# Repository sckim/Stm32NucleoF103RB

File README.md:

# Stm32NucleoF103RB

**임베디드시스템** 교과목의 실습 자료 저장소이다. STM32 Nucleo-F103RB(ARM Cortex-M3) 보드를 기준으로 GPIO부터 인터럽트, 타이머, ADC, UART, I2C까지 단계별 예제 프로젝트와 참고 문서, 회로 시뮬레이션 파일을 정리한다.

## 개발 환경

* IDE: [VS Code](https://code.visualstudio.com/) + [PlatformIO](https://platformio.org/) (예제 대부분), 일부는 STM32CubeIDE 프로젝트 파일(`.project`, `.cproject`, `.ioc`)을 함께 포함함
* 보드 설정: [STM32CubeMX](https://www.st.com/en/development-tools/stm32cubemx.html)로 생성한 `.ioc` 파일 기준
* 드라이버: STM32 HAL 및 LL(Low-Layer) 라이브러리, 일부 예제는 레지스터 직접 제어 방식
* 회로 시뮬레이션: [Proteus](https://www.labcenter.com/) (프로젝트 파일 `STM32F103R_ArduinoPinmap.pdsprj`는 각 예제 폴더에 있다). 파일이름은 같지만 내부 회로도가 조금씩 다를 수 있다.

## 폴더 구조

| 폴더/파일 | 내용 |
|---|---|
| `Docs/` | 데이터시트, 레퍼런스 매뉴얼 등 STM32F103 관련 공식 문서(PDF) |
| `Examples/` | 실습 예제 프로젝트 모음 |
| `Schematics/AD2_extension/` | AD2 확장 키트 KiCad 회로도/PCB ([README](Schematics/AD2_extension/README.md)) — 2026-10 `01_Lectures` 저장소의 `Schematics/AD2_extension`에서 이동 |

## 문서 활용법

이 저장소는 예제 코드와 함께 여러 층의 문서를 제공한다. 어디에 무엇이 있는지, 무엇을 먼저 여는지를 이 장에서 정리한다. 교안 전체를 어떤 순서로 보면 좋은지는 [교안의_활용법.html](교안의_활용법.html)에 더 자세히 있다.

### 1. 실습을 시작하기 전: 저장소 받기와 최신화

| 문서 | 내용 | 언제 보나 |
|---|---|---|
| [Examples/실습자료_최신화.pdf](Examples/실습자료_최신화.pdf) | VS Code에서 저장소를 클론하고, 수업 전에 Pull로 최신 자료를 받는 절차. 자주 만나는 상황표와 수업 전 체크리스트 | 처음 한 번, 그리고 매 수업 시작 전 |
| [Git_개념과_기본사용법.pdf](Git_개념과_기본사용법.pdf) | Git과 GitHub를 쓰는 이유, Git의 세 작업 공간, 커밋과 GitHub에 올리기, Clone·Pull·Fetch의 차이, 브랜치, 자주 쓰는 명령어, 수업에서 지킬 기본 습관 | 위 절차의 용어가 낯설 때, 내 변경을 기록하고 싶을 때 |

학생은 자료를 내려받기만 한다. 수업에서 지시하지 않았다면 Push나 Sync Changes는 누르지 않는다. 오류나 충돌이 나오면 파일을 지우지 말고 담당자에게 문의한다(자세한 상황표는 `실습자료_최신화.pdf` 4절).

### 2. 문서의 층: 어디에 무엇이 있는가

| 위치 | 문서 | 용도 |
|---|---|---|
| 저장소 루트 | 이 README | 저장소 전체 안내, 예제 목록, 참고 문서, 시뮬레이션 안내 |
| `Examples/` | [Examples/README.md](Examples/README.md) | 예제 전체 지도, 학습 순서, 명명 규칙 |
| 그룹 폴더 (예: `Examples/03_ADC/`) | **`<그룹명> 개념설명.html` (개념설명)** | 그 주변장치가 칩 안에서 어떻게 동작하는지를 원본 블록도와 신호 경로로 이해한다. 그룹별 링크는 아래 [그룹별 개념설명](#그룹별-개념설명)에 있다 |
| 그룹 폴더 | `README.md` | 그룹의 예제 목록, 공통 배선·핀, 배우는 것 |
| 예제 폴더 | `<예제명> 예제설명.html` (예제설명) | 그 예제의 코드를 레지스터·비트 단위로 해석하고, 시뮬레이터·실험·확인 문제로 확인한다. 아직 없는 예제도 있다 |
| 예제 폴더 | `README.md`, `main.c` 상단 주석 | 요약, 사용 레지스터·비트, ISR과 HAL 콜백의 역할 구분 |
| 예제 폴더 | `*.pdsprj`, (`Examples/01_GPIO/02_BlinkHAL`) `wokwi.toml`·`diagram.json` | 보드 없이 시뮬레이션한다. 설정과 제약은 아래 [회로 시뮬레이션](#회로-시뮬레이션) 참고 |
| `Docs/` | RM0008, 데이터시트 등 원본 PDF | 교안이 인용한 쪽을 직접 확인한다. [Docs/README.md](Docs/README.md)에 읽는 순서가 있다 |

### 3. 그룹 하나를 공부하는 순서 (권장)

1. **그룹 `README.md`**: 예제 목록과 필요한 배선을 확인한다.
2. **개념설명 1~3장**: 문제 정의, 일반 개념, 내부 구현 블록도를 먼저 읽는다. 개념과 신호의 흐름을 먼저 잡는다.
3. **예제설명과 코드**: 예제를 번호 순서대로 빌드하고 실행한다. 예제설명이 없는 예제는 예제 README와 `main.c` 주석을 본다.
4. **개념설명 4~7장**: 클럭·시간 계산, 제어 요소, 이벤트, 동작 시나리오를 실습한 예제와 연결해 다시 읽는다.
5. **개념설명 9장 확인 문제**로 점검한다. 답은 접혀 있으므로 먼저 풀어 본 뒤 연다.
6. **막히면** 개념설명 8장(설계상 한계와 정오표)을 보고, 그래도 모르면 `Docs/`의 원본 PDF로 간다.

개념설명 10장의 표는 "각 예제가 개념설명의 어느 장을 쓰는지"를 보여 준다. 예제를 하다가 개념이 막히면 이 표에서 해당 장으로 돌아간다.

### 4. 개념설명은 이렇게 읽는다

개념설명은 모든 그룹이 같은 10장 틀이다. 근거 문서, 인용·표기 약속, 그림 출처처럼 모든 교안에 공통인 내용은 [교안의_활용법.html](교안의_활용법.html)에 한 번만 적었고, 각 교안에는 그 교안만의 내용을 쓴다.

| 장 | 내용 | 이럴 때 본다 |
|---|---|---|
| 1 | 문제 정의 | 이 주변장치가 없으면 CPU가 무엇을 직접 해야 하는지 |
| 2 | 일반 개념 | 칩과 무관한, 디지털논리와 연결되는 기본 원리 |
| 3 | 내부 구현 블록도 | 신호가 핀에서 CPU까지 어떤 경로로 흐르는지 |
| 4 | 클럭 경로와 시간 계산 | 주파수·시간을 계산할 때(계산기 포함) |
| 5 | 제어 요소의 역할 | 레지스터 비트가 블록도의 어느 스위치인지 |
| 6 | 이벤트 생성 기전 | 플래그, 인터럽트, DMA 요청, 다른 주변장치 연결 |
| 7 | 동작 시나리오 | 한 번의 동작을 시간 순서의 타이밍도로 따라갈 때 |
| 8 | 설계상 한계와 이유 | 왜 이렇게 만들었는지, 정오표의 알려진 결함 |
| 9 | 이해 확인 문제 | 계산형·추론형 문제로 점검할 때 |
| 10 | 하부 예제 연결 | 어떤 예제가 이 경로를 쓰는지, 마지막 "정리" 상자 |

읽을 때 알아 둘 점은 다음과 같다.

- **브라우저로 연다.** `.html` 파일을 더블클릭하면 된다. 그림은 같은 그룹 폴더의 `img/`에, PDF 링크는 `Docs/`를 가리키므로 저장소 폴더 구조를 그대로 둔다.
- **그림 캡션의 "출처" 링크**를 누르면 원본 PDF의 그 쪽이 열린다. 교안의 모든 사실은 이렇게 문서의 쪽과 Figure·Table 번호로 확인할 수 있다.
- **"등가 모델" 표시**는 문서에 내부 구현이 없어 디지털논리 소자(카운터, 비교기, 시프트 레지스터 등)로 바꿔 그린 설명이라는 뜻이다. 실제 회로도가 아니다.
- **약어**는 처음 나올 때 풀어 쓰고, 앞쪽의 접힌 "약어 모음"에도 모아 두었다.
- **코드와 라이브러리 함수는 개념설명에 없다.** 코드는 예제설명과 `main.c`에서 다룬다.
- `Examples/12_Advanced_Topics`에는 개념설명이 없다.

## 실습 예제 (`Examples/`)

### 그룹별 개념설명

각 그룹의 주변장치 하드웨어를 원본 블록도와 디지털논리 관점으로 설명하는 문서이다(같은 10장 틀). 예제별 예제설명은 각 예제 폴더에 있다.

| 개념설명 |
|---|
| [01_GPIO](Examples/01_GPIO/01_GPIO%20개념설명.html) |
| [02_USART](Examples/02_USART/02_USART%20개념설명.html) |
| [03_ADC](Examples/03_ADC/03_ADC%20개념설명.html) |
| [04_I2C_Communication](Examples/04_I2C_Communication/04_I2C_Communication%20개념설명.html) |
| [05_SPI_Communication](Examples/05_SPI_Communication/05_SPI_Communication%20개념설명.html) |
| [06_Timers_RTC](Examples/06_Timers_RTC/06_Timers_RTC%20개념설명.html) |
| [07_DMA](Examples/07_DMA/07_DMA%20개념설명.html) |
| [08_Clock_System](Examples/08_Clock_System/08_Clock_System%20개념설명.html) |
| [09_WatchDog_Sleep](Examples/09_WatchDog_Sleep/09_WatchDog_Sleep%20개념설명.html) |
| [10_Flash_CRC](Examples/10_Flash_CRC/10_Flash_CRC%20개념설명.html) |
| [11_CAN_Communication](Examples/11_CAN_Communication/11_CAN_Communication%20개념설명.html) |

### 예제 목록

| 번호 | 예제 (`그룹/예제`) | 구현 방식 | 내용 |
|---|---|---|---|
| 01 | [`01_GPIO/01_BlinkArduino`](Examples/01_GPIO/01_BlinkArduino) | Arduino 프레임워크(PlatformIO) | `pinMode`/`digitalWrite`로 온보드 LED(PA5) 점멸 |
| 02 | [`01_GPIO/02_BlinkHAL`](Examples/01_GPIO/02_BlinkHAL) | HAL 드라이버 | HAL API 기반 LED 점멸 |
| 03 | [`01_GPIO/03_BlinkLL`](Examples/01_GPIO/03_BlinkLL) | LL 드라이버 | LL API 기반 LED 점멸 |
| 04 | [`01_GPIO/04_BlinkReg`](Examples/01_GPIO/04_BlinkReg) | 레지스터 직접 제어 | `RCC`, `GPIOx->CRL` 레지스터를 직접 조작하여 LED 점멸, SysTick 기반 딜레이 구현 |
| 05 | [`01_GPIO/05_ReadPin`](Examples/01_GPIO/05_ReadPin) | HAL | 사용자 버튼(B1) 폴링 입력으로 LED(LD2) 제어 |
| 06 | [`01_GPIO/06_ExtInt`](Examples/01_GPIO/06_ExtInt) | HAL, EXTI | 버튼 입력을 EXTI 인터럽트로 처리(`HAL_GPIO_EXTI_Callback`) |
| 07 | [`01_GPIO/07_ReadPinReg`](Examples/01_GPIO/07_ReadPinReg) | 레지스터 | `GPIOC->IDR` 직접 읽기로 버튼 폴링 (05_ReadPin의 레지스터 버전) |
| 08 | [`01_GPIO/08_ExternalInt`](Examples/01_GPIO/08_ExternalInt) | HAL, EXTI | 두 개 EXTI 라인(`EXTI9_5`, `EXTI15_10`)의 버튼 B1(PC13)·B2(PA6)를 하나의 `HAL_GPIO_EXTI_Callback`에서 구분 처리 |
| 09 | [`01_GPIO/09_BitBandingReg`](Examples/01_GPIO/09_BitBandingReg) | 레지스터 | Cortex-M3 비트 밴딩 별칭으로 RCC/GPIO/SRAM 비트를 원자적으로 접근 |
| 01 | [`02_USART/01_USART_printf`](Examples/02_USART/01_USART_printf) | HAL, UART | `printf` 출력을 USART로 리다이렉션 |
| 02 | [`02_USART/02_USART_Interrupt`](Examples/02_USART/02_USART_Interrupt) | HAL, UART, NVIC | USART2 수신 인터럽트(`HAL_UART_RxCpltCallback`)로 에코 및 LED 제어 |
| 03 | [`02_USART/03_USART_RingBuffer`](Examples/02_USART/03_USART_RingBuffer) | HAL, UART | ISR->main 링 버퍼(lock-free), 오버플로 시험(B1로 main 정지) |
| 04 | [`02_USART/04_USART_DMA_IdleLine_c`](Examples/02_USART/04_USART_DMA_IdleLine_c) | HAL, UART, DMA | (검토 전) DMA 원형 수신 + IDLE 라인 감지로 가변 길이 패킷 처리 |
| 05 | [`02_USART/05_UART_CLI_c`](Examples/02_USART/05_UART_CLI_c) | HAL, UART | (검토 전) 명령줄 인터페이스: 줄 편집, 명령 테이블(help/led/uptime/echo/peek/reset) |
| 06 | [`02_USART/06_USART_HalfDuplex_c`](Examples/02_USART/06_USART_HalfDuplex_c) | HAL, UART | (검토 전) USART 단선 반이중(PA9 한 선), 방향 전환, 오픈드레인 버스 |
| 07 | [`02_USART/07_USART_Stack`](Examples/02_USART/07_USART_Stack) | HAL, UART, CMSIS | 스택(LIFO) 괄호 검사기, ISR 공유 시 경쟁 상태와 PRIMASK 임계 구역 |
| 08 | [`02_USART/08_USART_printf_Dual`](Examples/02_USART/08_USART_printf_Dual) | HAL, UART | `printf`를 USART2(VCP)와 USART1(PA9=D8)로 동시 출력, AD2로 UART 파형 관찰 |
| 01 | [`03_ADC/01_ADC_Single`](Examples/03_ADC/01_ADC_Single) | HAL, ADC | 외부 핀 PA0(CH0) 한 채널 ADC 값을 UART로 출력 |
| 02 | [`03_ADC/02_ADC_Temperature`](Examples/03_ADC/02_ADC_Temperature) | HAL, ADC | 내부 온도 센서(CH16) 값을 섭씨로 환산해 UART로 출력 |
| 03 | [`03_ADC/03_ADC_Multi`](Examples/03_ADC/03_ADC_Multi) | HAL, ADC | 스캔 + 불연속 모드로 DMA 없이 4채널(A0/A1/A2/Vrefint) 폴링 |
| 04 | [`03_ADC/04_ADC_DMA_TimTrigger`](Examples/03_ADC/04_ADC_DMA_TimTrigger) | HAL, ADC, DMA, TIM | TIM3 TRGO 트리거 1kHz 2채널 스캔, DMA 원형 저장, HT/TC 콜백 |
| 05 | [`03_ADC/05_ADC_AnalogWatchdog_c`](Examples/03_ADC/05_ADC_AnalogWatchdog_c) | HAL, ADC, DMA | (검토 전) ADC 아날로그 워치독으로 전압 창(window) 이탈 감지 인터럽트 |
| 06 | [`03_ADC/06_ADC_Vrefint_VDDA_c`](Examples/03_ADC/06_ADC_Vrefint_VDDA_c) | HAL, ADC | (검토 전) Vrefint 로 실제 VDDA 를 측정해 ADC 값을 보정 |
| 07 | [`03_ADC/07_ADC_Potentiometer_PWM_c`](Examples/03_ADC/07_ADC_Potentiometer_PWM_c) | HAL, ADC, TIM | (검토 전) 가변저항 → 이동평균/히스테리시스/감마 → PWM 밝기 |
| 01 | [`04_I2C_Communication/01_I2C_Scan`](Examples/04_I2C_Communication/01_I2C_Scan) | HAL, I2C | I2C1 버스 스캐너(0x08~0x77), 흔한 장치 이름 표시 |
| 02 | [`04_I2C_Communication/02_PCF8574_Output`](Examples/04_I2C_Communication/02_PCF8574_Output) | HAL, I2C | PCF8574 기본: 1바이트로 핀 8개(P7~P0) 출력, 다시 읽어 비교, 액티브 Low LED |
| 03 | [`04_I2C_Communication/03_PCF8574_LCD`](Examples/04_I2C_Communication/03_PCF8574_LCD) | HAL, I2C | PCF8574 I2C 확장 IC를 통한 문자 LCD 제어, I2C 주소 스캐너 포함 |
| 04 | [`04_I2C_Communication/04_I2C_MPU6050_c`](Examples/04_I2C_Communication/04_I2C_MPU6050_c) | HAL, I2C | (검토 전) MPU6050 WHO_AM_I 확인과 가속도/자이로/온도 14바이트 연속 읽기 |
| 05 | [`04_I2C_Communication/05_I2C_MPU6050_DMA_c`](Examples/04_I2C_Communication/05_I2C_MPU6050_DMA_c) | HAL, I2C, DMA | (검토 전) 논블로킹 I2C(DMA)로 MPU6050 읽기, 오류 복구 |
| 06 | [`04_I2C_Communication/06_I2C_OLED_SSD1306_c`](Examples/04_I2C_Communication/06_I2C_OLED_SSD1306_c) | HAL, I2C | (검토 전) SSD1306 OLED, 프레임버퍼, 선/숫자/애니메이션 |
| 07 | [`04_I2C_Communication/07_I2C_EEPROM_AT24C_c`](Examples/04_I2C_Communication/07_I2C_EEPROM_AT24C_c) | HAL, I2C | (검토 전) AT24Cxx EEPROM: 16비트 주소, 페이지 경계, ACK 폴링 |
| 08 | [`04_I2C_Communication/08_I2C_DS3231_RTC_c`](Examples/04_I2C_Communication/08_I2C_DS3231_RTC_c) | HAL, I2C | (검토 전) 외장 RTC DS3231: BCD 시각, 온도, OSF 플래그 |
| 01 | [`05_SPI_Communication/01_SPI_Loopback_c`](Examples/05_SPI_Communication/01_SPI_Loopback_c) | HAL, SPI | (검토 전) SPI1 마스터 루프백(MOSI-MISO 점퍼), 분주비별 전송 속도 측정 |
| 02 | [`05_SPI_Communication/02_SPI_DMA_Fullduplex_c`](Examples/05_SPI_Communication/02_SPI_DMA_Fullduplex_c) | HAL, SPI, DMA | (검토 전) SPI1 전이중 DMA 전송, 폴링 방식과 시간/CPU 여유 비교 |
| 03 | [`05_SPI_Communication/03_SPI_OLED_SSD1306_c`](Examples/05_SPI_Communication/03_SPI_OLED_SSD1306_c) | HAL, SPI | (검토 전) SPI 로 SSD1306 OLED (D/C 핀, 8MHz) |
| 04 | [`05_SPI_Communication/04_SPI_SDcard_c`](Examples/05_SPI_Communication/04_SPI_SDcard_c) | HAL, SPI | (검토 전) SPI 모드 SD 카드 초기화, 섹터 읽기(MBR), 용량 계산 |
| 05 | [`05_SPI_Communication/05_SPI_Flash_W25Qxx_c`](Examples/05_SPI_Communication/05_SPI_Flash_W25Qxx_c) | HAL, SPI | (검토 전) SPI NOR Flash(W25Qxx): JEDEC ID, 섹터 소거, 페이지 프로그램 |
| 06 | [`05_SPI_Communication/06_SPI_MAX7219_c`](Examples/05_SPI_Communication/06_SPI_MAX7219_c) | HAL, SPI | (검토 전) MAX7219 8x8 LED 매트릭스, 16비트 프레임/LOAD 반영 |
| 01 | [`06_Timers_RTC/01_TIM_TimeBase`](Examples/06_Timers_RTC/01_TIM_TimeBase) | HAL, TIM | 타이머 주기 인터럽트(`HAL_TIM_PeriodElapsedCallback`)로 LED 토글 |
| 02 | [`06_Timers_RTC/02_TIM_TimeBase_Polling`](Examples/06_Timers_RTC/02_TIM_TimeBase_Polling) | HAL, TIM | 01의 폴링 버전: `SR.UIF` 직접 확인·클리어, printf 블로킹으로 인한 틱 누락(lag) 관찰 |
| 03 | [`06_Timers_RTC/03_TIM_Overflow_Counter`](Examples/06_Timers_RTC/03_TIM_Overflow_Counter) | HAL+레지스터, TIM | 오버플로 횟수(`gOvf`)를 상위 16비트로 붙인 32비트 µs 시계, 두 번 읽기 경쟁 조건과 UIF 보정
| 04 | [`06_Timers_RTC/04_TIM_OutputCompare`](Examples/06_Timers_RTC/04_TIM_OutputCompare) | HAL, TIM | 출력 비교 Toggle/Timing 모드, CCR 전진으로 채널별 주파수
| 05 | [`06_Timers_RTC/05_TIM_PWM`](Examples/06_Timers_RTC/05_TIM_PWM) | HAL, TIM | TIM2_CH1(PA0) 1kHz PWM, LED 밝기 왕복 |
| 06 | [`06_Timers_RTC/06_TIM_InputCapture_c`](Examples/06_Timers_RTC/06_TIM_InputCapture_c) | HAL, TIM | (검토 전) 입력 캡처로 주기/주파수 측정 (TIM3 PWM 테스트 신호 포함) |
| 07 | [`06_Timers_RTC/07_TIM_PWMInput_c`](Examples/06_Timers_RTC/07_TIM_PWMInput_c) | HAL, TIM | (검토 전) PWM 입력 모드(슬레이브 리셋)로 주파수/듀티 하드웨어 측정 |
| 08 | [`06_Timers_RTC/08_TIM1_DeadTime_Break_c`](Examples/06_Timers_RTC/08_TIM1_DeadTime_Break_c) | HAL, TIM1 | (검토 전) 상보 PWM + 데드타임(약 1us) + 브레이크 입력/소프트웨어 브레이크 |
| 09 | [`06_Timers_RTC/09_TIM_Encoder_c`](Examples/06_Timers_RTC/09_TIM_Encoder_c) | HAL, TIM | (검토 전) 엔코더 인터페이스 모드(x4), 소프트웨어 직교 신호 시뮬레이션 포함 |
| 10 | [`06_Timers_RTC/10_TIM_OnePulse_HCSR04_c`](Examples/06_Timers_RTC/10_TIM_OnePulse_HCSR04_c) | HAL, TIM | (검토 전) 원 펄스 모드 10us 트리거 + 입력 캡처로 HC-SR04 거리 측정 |
| 11 | [`06_Timers_RTC/11_TIM_Servo_c`](Examples/06_Timers_RTC/11_TIM_Servo_c) | HAL, TIM | (검토 전) RC 서보: 50Hz PWM, 1~2ms = 0~180° |
| 12 | [`06_Timers_RTC/12_TIM_MotorDriver_TB6612_c`](Examples/06_Timers_RTC/12_TIM_MotorDriver_TB6612_c) | HAL, TIM | (검토 전) H-브리지 모터: 20kHz PWM, 쇼트 브레이크/코스트, 비상 정지 |
| 13 | [`06_Timers_RTC/13_RTC_Calendar_c`](Examples/06_Timers_RTC/13_RTC_Calendar_c) | HAL+레지스터, RTC | (검토 전) F1 RTC(32비트 카운터)를 Unix 시간으로 쓰는 달력 시계, 1초 인터럽트 |
| 01 | [`07_DMA/01_DMA_MemToMem`](Examples/07_DMA/01_DMA_MemToMem) | HAL, DMA | 메모리->메모리 DMA 복사, CPU 복사와 DWT 사이클 비교 |
| 02 | [`07_DMA/02_DMA_Circular_GPIO`](Examples/07_DMA/02_DMA_Circular_GPIO) | HAL, DMA, TIM | 원형 DMA + 핑퐁 버퍼로 GPIOC 패턴 자동 출력 |
| 01 | [`08_Clock_System/01_CoreRegisters_Instructions_Reg_c`](Examples/08_Clock_System/01_CoreRegisters_Instructions_Reg_c) | 레지스터+ASM | (검토 전) 레지스터 파일, 조건 플래그, IT 조건부실행, 스택 PUSH/POP, 하드웨어 나눗셈 |
| 02 | [`08_Clock_System/02_MemoryMap_Reg_c`](Examples/08_Clock_System/02_MemoryMap_Reg_c) | 레지스터 | (검토 전) 4GB 주소 공간, 버스 계층, memory-mapped I/O, 리틀 엔디안 |
| 03 | [`08_Clock_System/03_ExceptionModel_VectorTable_Reg_c`](Examples/08_Clock_System/03_ExceptionModel_VectorTable_Reg_c) | 레지스터+ASM | (검토 전) 벡터 테이블, 예외 자동 스택 저장, EXC_RETURN, SVC |
| 04 | [`08_Clock_System/04_Clock_Config_Reg_c`](Examples/08_Clock_System/04_Clock_Config_Reg_c) | 레지스터 | (검토 전) RCC/FLASH 레지스터로 HSI 8MHz <-> PLL 48MHz 전환, MCO 출력 |
| 05 | [`08_Clock_System/05_SysTick_Reg_c`](Examples/08_Clock_System/05_SysTick_Reg_c) | 레지스터 | (검토 전) SysTick 1ms 틱, `millis()`, 논블로킹 LED/버튼 처리 |
| 06 | [`08_Clock_System/06_NVIC_Priority_c`](Examples/08_Clock_System/06_NVIC_Priority_c) | HAL, NVIC | (검토 전) 선점/서브 우선순위와 인터럽트 중첩 실험, B1로 3가지 케이스 전환 |
| 07 | [`08_Clock_System/07_AFIO_Remap_Reg_c`](Examples/08_Clock_System/07_AFIO_Remap_Reg_c) | 레지스터 | (검토 전) AFIO_MAPR로 JTAG 핀(PB3/PB4/PA15) 해방과 TIM2 핀 리맵 |
| 08 | [`08_Clock_System/08_HardFault_Diagnosis_Reg_c`](Examples/08_Clock_System/08_HardFault_Diagnosis_Reg_c) | 레지스터+어셈블리 | (검토 전) 4종 폴트 유발, 스택 프레임/CFSR/BFAR 해석해 UART 출력 |
| 09 | [`08_Clock_System/09_MCO_ClockOut_c`](Examples/08_Clock_System/09_MCO_ClockOut_c) | HAL, RCC | (검토 전) MCO(PA8)로 HSI/PLL/HSE 클럭 출력, B1로 소스 순환 |
| 10 | [`08_Clock_System/10_DWT_Profiling_Reg_c`](Examples/08_Clock_System/10_DWT_Profiling_Reg_c) | 레지스터 | (검토 전) DWT 사이클 카운터로 연산/함수 실행 시간(사이클) 측정 |
| 11 | [`08_Clock_System/11_NonBlocking_StateMachine_c`](Examples/08_Clock_System/11_NonBlocking_StateMachine_c) | HAL | (검토 전) HAL_Delay 없는 상태 머신 신호등, 버튼 디바운스/이벤트 |
| 12 | [`08_Clock_System/12_DeviceInfo_UniqueID_Reg_c`](Examples/08_Clock_System/12_DeviceInfo_UniqueID_Reg_c) | 레지스터 | (검토 전) 96비트 고유 ID, 플래시 크기, DEV_ID, 리셋 원인 출력 |
| 01 | [`09_WatchDog_Sleep/01_WatchdogTimer`](Examples/09_WatchDog_Sleep/01_WatchdogTimer) | HAL, WWDG | 윈도우 워치독(WWDG) 초기화와 주기적 리프레시 기본 사용 |
| 02 | [`09_WatchDog_Sleep/02_WWDG_c`](Examples/09_WatchDog_Sleep/02_WWDG_c) | HAL, WWDG | (검토 전) 윈도우 워치독(너무 이른/늦은 리프레시 리셋), 조기 경고 콜백 |
| 03 | [`09_WatchDog_Sleep/03_Sleep_Mode_c`](Examples/09_WatchDog_Sleep/03_Sleep_Mode_c) | HAL, PWR | (검토 전) WFI Sleep 모드, 바쁜 대기와 main 루프 횟수 비교 |
| 04 | [`09_WatchDog_Sleep/04_Stop_Mode_EXTI_c`](Examples/09_WatchDog_Sleep/04_Stop_Mode_EXTI_c) | HAL, PWR, EXTI | (검토 전) Stop 모드 진입, 버튼(EXTI) 웨이크업 후 클럭 복구 |
| 05 | [`09_WatchDog_Sleep/05_Standby_RTC_Wakeup_c`](Examples/09_WatchDog_Sleep/05_Standby_RTC_Wakeup_c) | HAL, PWR, RTC | (검토 전) Standby 진입, RTC 알람(10초) 웨이크업, BKP 부팅 카운터 유지 |
| 06 | [`09_WatchDog_Sleep/06_BKP_Tamper_c`](Examples/09_WatchDog_Sleep/06_BKP_Tamper_c) | HAL+레지스터, BKP | (검토 전) 백업 레지스터 유지, TAMPER(PC13) 감지 시 삭제 |
| 07 | [`09_WatchDog_Sleep/07_IWDG_c`](Examples/09_WatchDog_Sleep/07_IWDG_c) | HAL, IWDG | (검토 전) 독립 워치독(LSI), 타임아웃 계산, 리셋 원인 |
| 01 | [`10_Flash_CRC/01_Flash_Write_c`](Examples/10_Flash_CRC/01_Flash_Write_c) | HAL, FLASH | (검토 전) 내부 Flash 페이지에 부팅 횟수 덧붙여 저장(웨어 레벨링) |
| 02 | [`10_Flash_CRC/02_CRC_Unit_c`](Examples/10_Flash_CRC/02_CRC_Unit_c) | HAL, CRC | (검토 전) 하드웨어 CRC-32/MPEG-2와 소프트웨어 구현 비교, 1비트 오류 검출 |
| 01 | [`11_CAN_Communication/01_CAN_Loopback_c`](Examples/11_CAN_Communication/01_CAN_Loopback_c) | HAL, CAN | (검토 전) bxCAN 500kbps 루프백 송수신(트랜시버 불필요), FIFO0 수신 콜백 |
| 02 | [`11_CAN_Communication/02_CAN_Filter_c`](Examples/11_CAN_Communication/02_CAN_Filter_c) | HAL, CAN | (검토 전) bxCAN 수신 필터: ID 리스트/마스크, 표준·확장, FIFO0/1 |
| 01 | [`12_Advanced_Topics/01_ADC_Injected_c`](Examples/12_Advanced_Topics/01_ADC_Injected_c) | HAL, ADC, DMA | (검토 전) 주입 채널이 정규 연속 변환에 끼어들어 온도 센서를 읽음 |
| 02 | [`12_Advanced_Topics/02_ADC_DualMode_c`](Examples/12_Advanced_Topics/02_ADC_DualMode_c) | HAL, ADC, DMA | (검토 전) ADC1+ADC2 동시 샘플링(듀얼 모드), 32비트 DMA |
| 03 | [`12_Advanced_Topics/03_I2C_Slave_Loopback_c`](Examples/12_Advanced_Topics/03_I2C_Slave_Loopback_c) | HAL, I2C | (검토 전) I2C 슬레이브 모드(I2C1 마스터 ↔ I2C2 슬레이브), 리슨/주소 콜백 |
| 04 | [`12_Advanced_Topics/04_SPI_Slave_Loopback_c`](Examples/12_Advanced_Topics/04_SPI_Slave_Loopback_c) | HAL, SPI | (검토 전) SPI 슬레이브 모드(SPI1 마스터 ↔ SPI2 슬레이브), 하드웨어 NSS |
| 05 | [`12_Advanced_Topics/05_TIM_Cascade32_c`](Examples/12_Advanced_Topics/05_TIM_Cascade32_c) | HAL, TIM | (검토 전) 마스터/슬레이브로 잇는 32비트 카운터(71분), 스톱워치 |
| 06 | [`12_Advanced_Topics/06_DMA_Priority_c`](Examples/12_Advanced_Topics/06_DMA_Priority_c) | HAL, DMA | (검토 전) DMA 채널 우선순위/중재, 완료 시각 DWT 측정 |
| 07 | [`12_Advanced_Topics/07_PendSV_ContextSwitch_Reg_c`](Examples/12_Advanced_Topics/07_PendSV_ContextSwitch_Reg_c) | 레지스터+어셈블리 | (검토 전) SVC/PendSV/PSP 기반 미니 선점형 RTOS(작업 2개 시분할) |
| 08 | [`12_Advanced_Topics/08_HSE_PLL_72MHz_Reg_c`](Examples/12_Advanced_Topics/08_HSE_PLL_72MHz_Reg_c) | 레지스터 | (검토 전) HSE(바이패스)+PLL x9 = 72MHz, 실패 시 HSI 로 복귀 |
| 09 | [`12_Advanced_Topics/09_ITM_SWO_Printf_Reg_c`](Examples/12_Advanced_Topics/09_ITM_SWO_Printf_Reg_c) | 레지스터 | (검토 전) ITM/SWO 로 printf (UART 핀 불필요) |
| 10 | [`12_Advanced_Topics/10_StackWatermark_Reg_c`](Examples/12_Advanced_Topics/10_StackWatermark_Reg_c) | 레지스터 | (검토 전) 스택 페인팅과 하이 워터마크, 재귀 실험 |
| 11 | [`12_Advanced_Topics/11_IAP_Bootloader_Reg_c`](Examples/12_Advanced_Topics/11_IAP_Bootloader_Reg_c) | 레지스터 | (검토 전) IAP 부트로더: 앱 유효성 검사 후 VTOR 교체·점프 (링커 스크립트 포함) |
| 12 | [`12_Advanced_Topics/12_IAP_App_Reg_c`](Examples/12_Advanced_Topics/12_IAP_App_Reg_c) | 레지스터 | (검토 전) 0x08008000 에서 도는 IAP 응용 프로그램 (부트로더와 짝) |
| 13 | [`12_Advanced_Topics/13_IAP_Xmodem_Bootloader_Reg_c`](Examples/12_Advanced_Topics/13_IAP_Xmodem_Bootloader_Reg_c) | 레지스터 | (검토 전) UART XMODEM-CRC 로 펌웨어 수신·Flash 기록·점프하는 부트로더 |
| 14 | [`12_Advanced_Topics/14_OptionBytes_Read_c`](Examples/12_Advanced_Topics/14_OptionBytes_Read_c) | HAL, FLASH | (검토 전) 옵션 바이트 읽기(RDP/WRP/USER), 읽기 전용 |
| 15 | [`12_Advanced_Topics/15_CAN_Normal_2boards_c`](Examples/12_Advanced_Topics/15_CAN_Normal_2boards_c) | HAL, CAN | (검토 전) 실제 CAN 버스(2보드): 오류 카운터, 버스오프 복구 |

예제는 기능별 그룹 폴더 아래에 있고, **예제 폴더 번호는 그룹 안에서 항상 `01`부터 순서대로** 붙인다. 폴더명 끝의 `_c`는 Claude가 작성한 예제(검토 전)를 뜻한다. `12_Advanced_Topics`는 3학년 2학기 기본 진도를 넘어서는 **심화(선택)** 예제만 모아 둔 그룹이며, 나머지 01~11 그룹이 한 학기 분량이다. 그룹별 안내는 [Examples/README.md](Examples/README.md) 참고.

각 예제 폴더는 PlatformIO 프로젝트(`platformio.ini` 포함) 또는 STM32CubeIDE 프로젝트(`.project`/`.cproject`/`.ioc` 포함) 형태이며, VS Code에서 PlatformIO 확장으로 열어 빌드·업로드하는 것을 기본으로 한다.

## 참고 문서 (`Docs/`)

각 문서의 용도, 처음 읽는 순서, RM0008/PM0056 장 지도, 보드 클럭 구성은 [Docs/README.md](Docs/README.md) 에 정리되어 있다.

| 문서 | 설명 |
|---|---|
| [UM1724](Docs/UM1724_User_Manual_STM32Nucleo64.pdf) | Nucleo-64 보드 사용자 매뉴얼 |
| [DS5319 (데이터시트)](Docs/Datasheet_stm32f103.pdf) | STM32F103x8/xB 데이터시트 |
| [RM0008](Docs/RM0008_Reference_manual.pdf) | STM32F101/102/103/105/107 레지스터 레퍼런스 매뉴얼 |
| [PM0056](Docs/PM0056_CortexM3_Programming_Manual.pdf) | Cortex-M3 프로그래밍 매뉴얼 |
| [UM1850](Docs/HAL_UM1850_hal_and_lowlayer_drivers.pdf) | STM32F1 HAL/LL 드라이버 사용자 매뉴얼 |
| [MB1136 회로도](Docs/Schematic_STM32F103RB.pdf) | Nucleo-F103RB 보드 회로도 |
| [UM1718 (st.com)](https://www.st.com/resource/en/user_manual/um1718-stm32cubemx.pdf) | STM32CubeMX 사용자 매뉴얼 (77MB라 저장소에 넣지 않고 ST 사이트로 연결) |
| [PM0075](Docs/PM0075-stm32f10xxx-flash-memory.pdf) | STM32F10xxx Flash 메모리 프로그래밍 매뉴얼(쓰기·지우기·옵션 바이트) |
| [ES096](Docs/ES096_F103x8xB_Errata.pdf) | STM32F103x8/xB(중밀도, F103RB) 디바이스 errata(오류 정정표) |
| [AN2834](https://github.com/sckim/Stm32NucleoF103RB/blob/main/Docs/AN2834_ADC_Accuracy.pdf) | ADC 정확도 최적화 |
| [AN4013](https://github.com/sckim/Stm32NucleoF103RB/blob/main/Docs/AN4013_Timers_Introduction.pdf) | STM32 타이머 개요 |
| [AN4776](https://github.com/sckim/Stm32NucleoF103RB/blob/main/Docs/AN4776_General_Purpose_Timer.pdf) | 범용 타이머 활용 |
| [AN2548](https://github.com/sckim/Stm32NucleoF103RB/blob/main/Docs/AN2548_DMA_Controller.pdf) | DMA 컨트롤러 사용법 |
| [AN2586](Docs/AN2586_Hardware_Development_Getting_Started.pdf) | STM32F10xxx 하드웨어 개발 시작 가이드 |
| [AN2606](Docs/AN2606_System_Memory_Boot_Mode.pdf) | STM32 시스템 메모리 부트 모드(부트로더) |
| [DB2196](Docs/DB2196_Nucleo_64_boards.pdf) | Nucleo-64 보드 데이터브리프 |
| [UM1727](Docs/UM1727_Getting_started.pdf) | Nucleo 보드 시작하기 가이드(2016, 오래된 도구 기준) |
| [NUCLEO-F103RB 제품 페이지 (st.com)](https://www.st.com/en/evaluation-tools/nucleo-f103rb.html?ecmp=tt9470_gl_link_feb2019&rt=db&id=DB2196) | ST 공식 제품 페이지 (`Docs/NUCLEO-F103RB.url` 바로가기와 같은 주소) |

## 회로 시뮬레이션
Proteus 프로젝트는 각 예제 폴더에 있다. 파일 이름은 `STM32F103R_ArduinoPinmap.pdsprj`이다(`01_GPIO/07_ReadPinReg`만 `STM32F103R.pdsprj`). Proteus에서 열 때 MCU의 펌웨어 경로(`firmware.elf`)를 해당 예제의 빌드 결과로 지정한다.

### Proteus의 MCU 모델: F103RB 대신 F103C8

Proteus(8.17 기준) 라이브러리에는 **STM32F103RB 모델이 없다**. 제공되는 STM32F103 부품은 C4, C6, C8, R4, R6, T4, T6뿐이다. 그래서 프로젝트의 MCU는 그중 F103RB와 같은 medium-density 칩인 **STM32F103C8**(48핀)을 쓴다. 파일 이름에 `R`이 들어 있지만 실제 MCU는 C8이다.

| 항목 | STM32F103C8 (Proteus) | STM32F103RB (Nucleo) |
|---|---|---|
| 계열 | medium-density | medium-density |
| SRAM | 20 KB | 20 KB |
| 주변장치 | TIM1~4, SPI1~2, I2C1~2, USART1~3, USB, CAN | 같음 |
| Flash | **64 KB** | 128 KB |
| 패키지 / GPIO | **48핀 / 37개** | 64핀 / 51개 |

같은 계열이라 레지스터 주소, 주변장치 구성, 인터럽트 벡터, DMA 채널 배정은 같다(DS5319 Table 2). 차이는 Flash 크기와 핀 수이다.

- **포트 C가 거의 없다**: 48핀 패키지에는 **PC0~PC12와 PD2가 없고, 포트 C는 PC13~PC15만 있다**. Nucleo Arduino 헤더 가운데 포트 C에 연결된 핀(D9 = PC7, A4 = PC1, A5 = PC0 등)을 쓰는 예제는 Proteus에서 그 핀을 시뮬레이션할 수 없다(예: `01_GPIO/10_AD2Test`). PA·PB 핀과 PC13(사용자 버튼 B1)만 쓰는 예제는 문제없다.
- **Flash 64 KB**: 펌웨어가 64 KB를 넘으면 C8 모델에 올라가지 않는다. 현재 예제들은 대부분 이보다 훨씬 작다.
- 64핀 R6 모델은 핀은 맞지만 low-density 칩이다. Flash가 작고 TIM4·USART3·I2C2·SPI2 같은 medium-density 주변장치가 없어 RB용 펌웨어와 맞지 않는다.

Proteus의 STM32 모델 파일에는 DMA, RTC, IWDG, WWDG, ADC, USB 등의 모델이 들어 있다. 반면 **저전력 모드(PWR의 Sleep/Stop/Standby), 백업 레지스터·탬퍼(BKP), CAN은 모델링되어 있지 않은 것으로 보인다**. 이 판단은 설치된 모델 파일을 분석한 결과이다(Labcenter의 공식 목록은 없다). `09_WatchDog_Sleep`의 저전력·BKP 예제와 `11_CAN_Communication`은 실제 보드로 확인한다.

### Wokwi

`01_GPIO/02_BlinkHAL`에는 [Wokwi](https://wokwi.com) 시뮬레이터 설정(`wokwi.toml`, `diagram.json`)도 있다. Wokwi 역시 F103RB가 없어 Blue Pill(STM32F103C8)을 쓰며, DMA·RTC·PWR·IWDG는 지원하지 않는다. 사용법은 그 예제의 README를 참고한다.

## 관련 교과목
- 디지털논리회로, 디지털시스템, 마이크로컨트롤러
- 프로그래밍 언어 (C or C++)
- 회로이론, 전자회로

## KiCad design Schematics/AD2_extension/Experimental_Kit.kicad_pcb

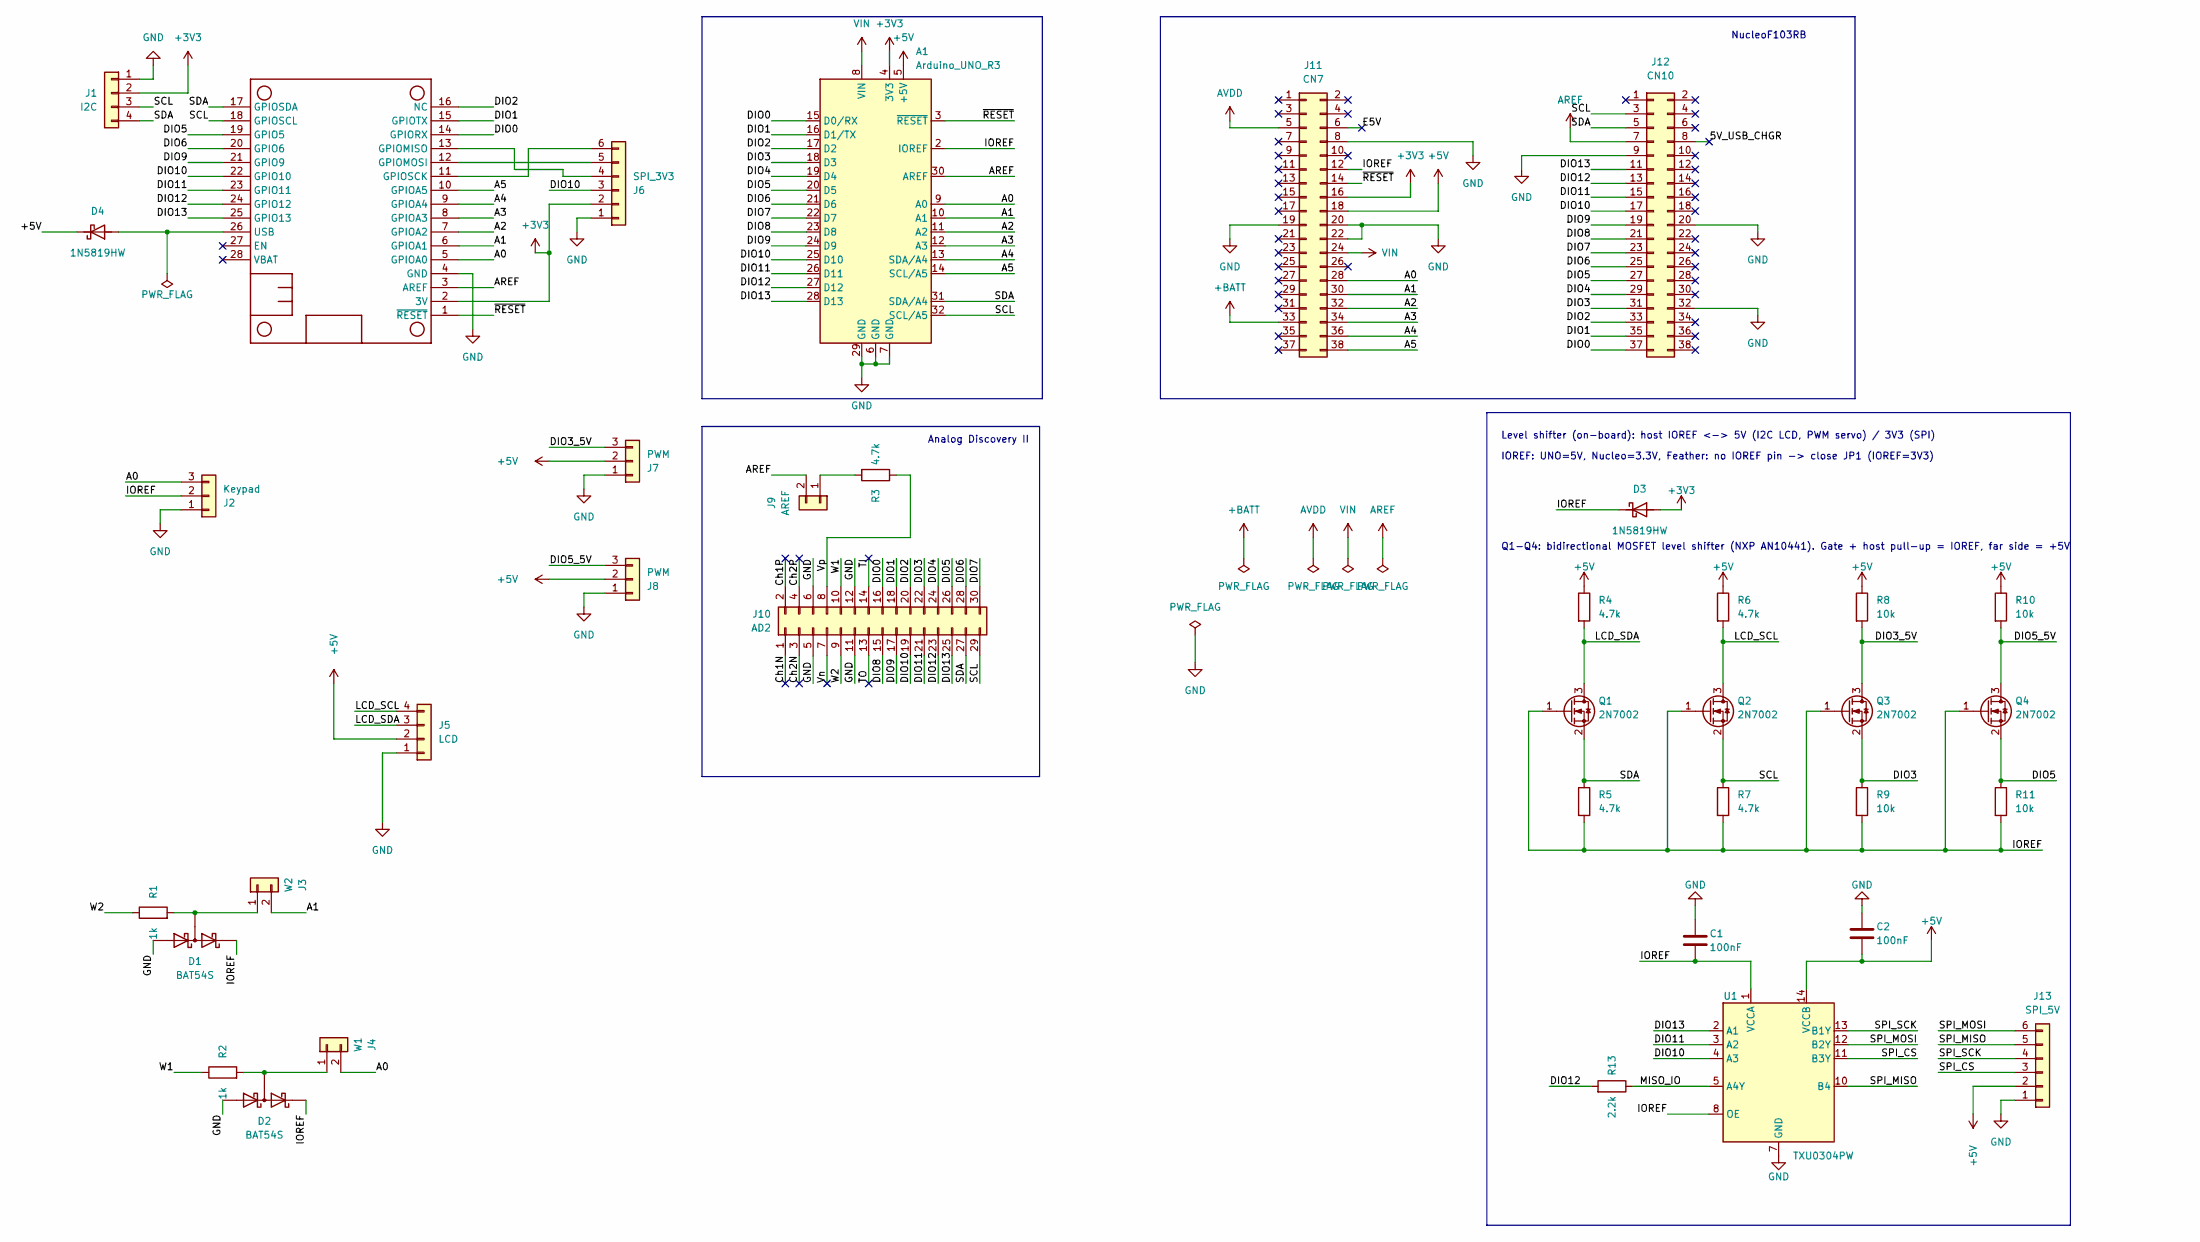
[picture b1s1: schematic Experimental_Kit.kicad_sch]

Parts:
A1: Arduino_UNO_R3; Arduino_UNO_R3_ShieldHeaders
C1, C2: 100nF; C_0805_2012Metric_Pad1.18x1.45mm_HandSolder
D1, D2: BAT54S; SOT-23
D3, D4: 1N5819HW; D_SOD-123
J1: I2C; PinHeader_1x04_P2.54mm_Vertical
J2: Keypad; PinHeader_1x03_P2.54mm_Vertical
J3: W2; PinHeader_1x02_P2.54mm_Vertical
J4: W1; PinHeader_1x02_P2.54mm_Vertical
J5: LCD; PinHeader_1x04_P2.54mm_Vertical
J6: SPI_3V3; PinHeader_1x06_P2.54mm_Vertical
J7, J8: PWM; PinHeader_1x03_P2.54mm_Vertical
J9: AREF; PinHeader_1x02_P2.54mm_Vertical
J10: AD2; PinSocket_2x15_P2.54mm_Horizontal_BoardEdge
J11: CN7; PinSocket_2x19_P2.54mm_Vertical_Mirrored
J12: CN10; PinSocket_2x19_P2.54mm_Vertical_Mirrored
J13: SPI_5V; PinHeader_1x06_P2.54mm_Vertical
MS1: FEATHERWING_NODIM
Q1, Q2, Q3, Q4: 2N7002; SOT-23
R1, R2: 1k; R_0805_2012Metric_Pad1.20x1.40mm_HandSolder
R3, R4, R5, R6, R7: 4.7k; R_0805_2012Metric_Pad1.20x1.40mm_HandSolder
R8, R9, R10, R11: 10k; R_0805_2012Metric_Pad1.20x1.40mm_HandSolder
R13: 2.2k; R_0805_2012Metric_Pad1.20x1.40mm_HandSolder
U1: TXU0304PW; TSSOP-14_4.4x5mm_P0.65mm

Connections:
+3V3: A1.4 (3V3), D3.2 (A), J1.2, J6.2, J11.16, MS1.2 (3V)
+5V: A1.5 (+5V), C2.2, D4.1 (K), J5.2, J7.2, J8.2, J11.18, J13.2, R4.1, R6.1, R8.1, R10.1, U1.14 (VCCB)
+BATT: J11.33
/5V_USB_CHGR: J12.8
/A0: A1.9 (A0), J2.3, J4.2, J11.28, MS1.5 (GPIOA0)
/A1: A1.10 (A1), J3.2, J11.30, MS1.6 (GPIOA1)
/A2: A1.11 (A2), J11.32, MS1.7 (GPIOA2)
/A3: A1.12 (A3), J11.34, MS1.8 (GPIOA3)
/A4: A1.13 (SDA/A4), J11.36, MS1.9 (GPIOA4)
/A5: A1.14 (SCL/A5), J11.38, MS1.10 (GPIOA5)
/Ch1N: J10.1
/Ch1P: J10.2
/Ch2N: J10.3
/Ch2P: J10.4
/DIO0: A1.15 (D0/RX), J10.16, J12.37, MS1.14 (GPIORX)
/DIO1: A1.16 (D1/TX), J10.18, J12.35, MS1.15 (GPIOTX)
/DIO2: A1.17 (D2), J10.20, J12.33, MS1.16 (NC)
/DIO3: A1.18 (D3), J10.22, J12.31, Q3.2 (S), R9.1
/DIO3_5V: J7.3, Q3.3 (D), R8.2
/DIO4: A1.19 (D4), J10.24, J12.29
/DIO5: A1.20 (D5), J10.26, J12.27, MS1.19 (GPIO5), Q4.2 (S), R11.1
/DIO5_5V: J8.3, Q4.3 (D), R10.2
/DIO6: A1.21 (D6), J10.28, J12.25, MS1.20 (GPIO6)
/DIO7: A1.22 (D7), J10.30, J12.23
/DIO8: A1.23 (D8), J10.15, J12.21
/DIO9: A1.24 (D9), J10.17, J12.19, MS1.21 (GPIO9)
/DIO10: A1.25 (D10), J6.3, J10.19, J12.17, MS1.22 (GPIO10), U1.4 (A3)
/DIO11: A1.26 (D11), J10.21, J12.15, MS1.23 (GPIO11), U1.3 (A2)
/DIO12: A1.27 (D12), J10.23, J12.13, MS1.24 (GPIO12), R13.2
/DIO13: A1.28 (D13), J10.25, J12.11, MS1.25 (GPIO13), U1.2 (A1)
/E5V: J11.6
/IOREF: A1.2 (IOREF), C1.2, D1.2 (K2), D2.2 (K2), D3.1 (K), J2.2, J11.12, Q1.1 (G), Q2.1 (G), Q3.1 (G), Q4.1 (G), R5.2, R7.2, R9.2, R11.2, U1.1 (VCCA), U1.8 (OE)
/LCD_SCL: J5.4, Q2.3 (D), R6.2
/LCD_SDA: J5.3, Q1.3 (D), R4.2
/MISO_IO: R13.1, U1.5 (A4Y)
/SCL: A1.32 (SCL/A5), J1.3, J10.29, J12.3, MS1.18 (GPIOSCL), Q2.2 (S), R7.1
/SDA: A1.31 (SDA/A4), J1.4, J10.27, J12.5, MS1.17 (GPIOSDA), Q1.2 (S), R5.1
/SPI_CS: J13.3, U1.11 (B3Y)
/SPI_MISO: J13.5, U1.10 (B4)
/SPI_MOSI: J13.6, U1.12 (B2Y)
/SPI_SCK: J13.4, U1.13 (B1Y)
/TI: J10.14
/TO: J10.13
/Vn: J10.7
/Vp: J10.8, R3.1
/W1: J10.10, R2.1
/W2: J10.9, R1.1
/~RESET: A1.3 (~RESET), J11.14, MS1.1 (~RESET)
AREF: A1.30 (AREF), J9.2, J12.7, MS1.3 (AREF)
AVDD: J11.5
GND: A1.6 (GND), A1.7 (GND), A1.29 (GND), C1.1, C2.1, D1.1 (A1), D2.1 (A1), J1.1, J2.1, J5.1, J6.1, J7.1, J8.1, J10.5, J10.6, J10.11, J10.12, J11.8, J11.19, J11.20, J11.22, J12.9, J12.20, J12.32, J13.1, MS1.4 (GND), U1.7 (GND)
unnamed: D1.3 (K1A2), J3.1, R1.2
unnamed: D2.3 (K1A2), J4.1, R2.2
unnamed: D4.2 (A), MS1.26 (USB)
unnamed: J6.4, MS1.13 (GPIOMISO)
unnamed: J6.5, MS1.12 (GPIOMOSI)
unnamed: J6.6, MS1.11 (GPIOSCK)
unnamed: J9.1, R3.2
VIN: A1.8 (VIN), J11.24

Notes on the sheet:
Level shifter (on-board): host IOREF <-> 5V (I2C LCD, PWM servo) / 3V3 (SPI)
IOREF: UNO=5V, Nucleo=3.3V, Feather: no IOREF pin -> close JP1 (IOREF=3V3)
Q1-Q4: bidirectional MOSFET level shifter (NXP AN10441). Gate + host pull-up = IOREF, far side = +5V
NucleoF103RB
Analog Discovery II

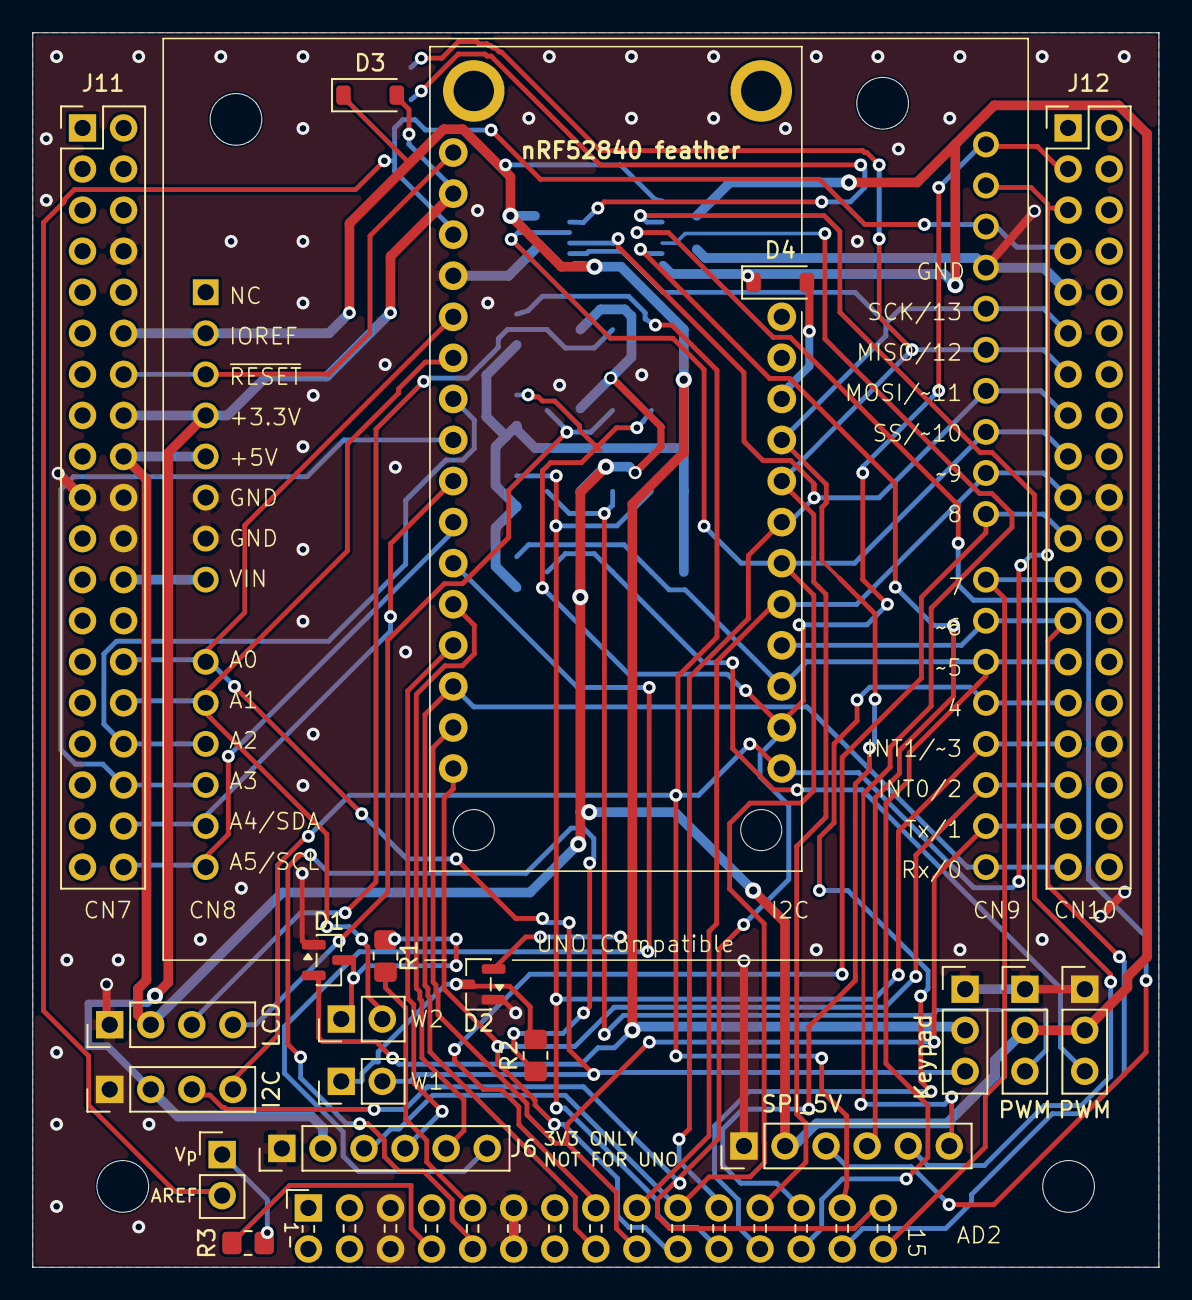
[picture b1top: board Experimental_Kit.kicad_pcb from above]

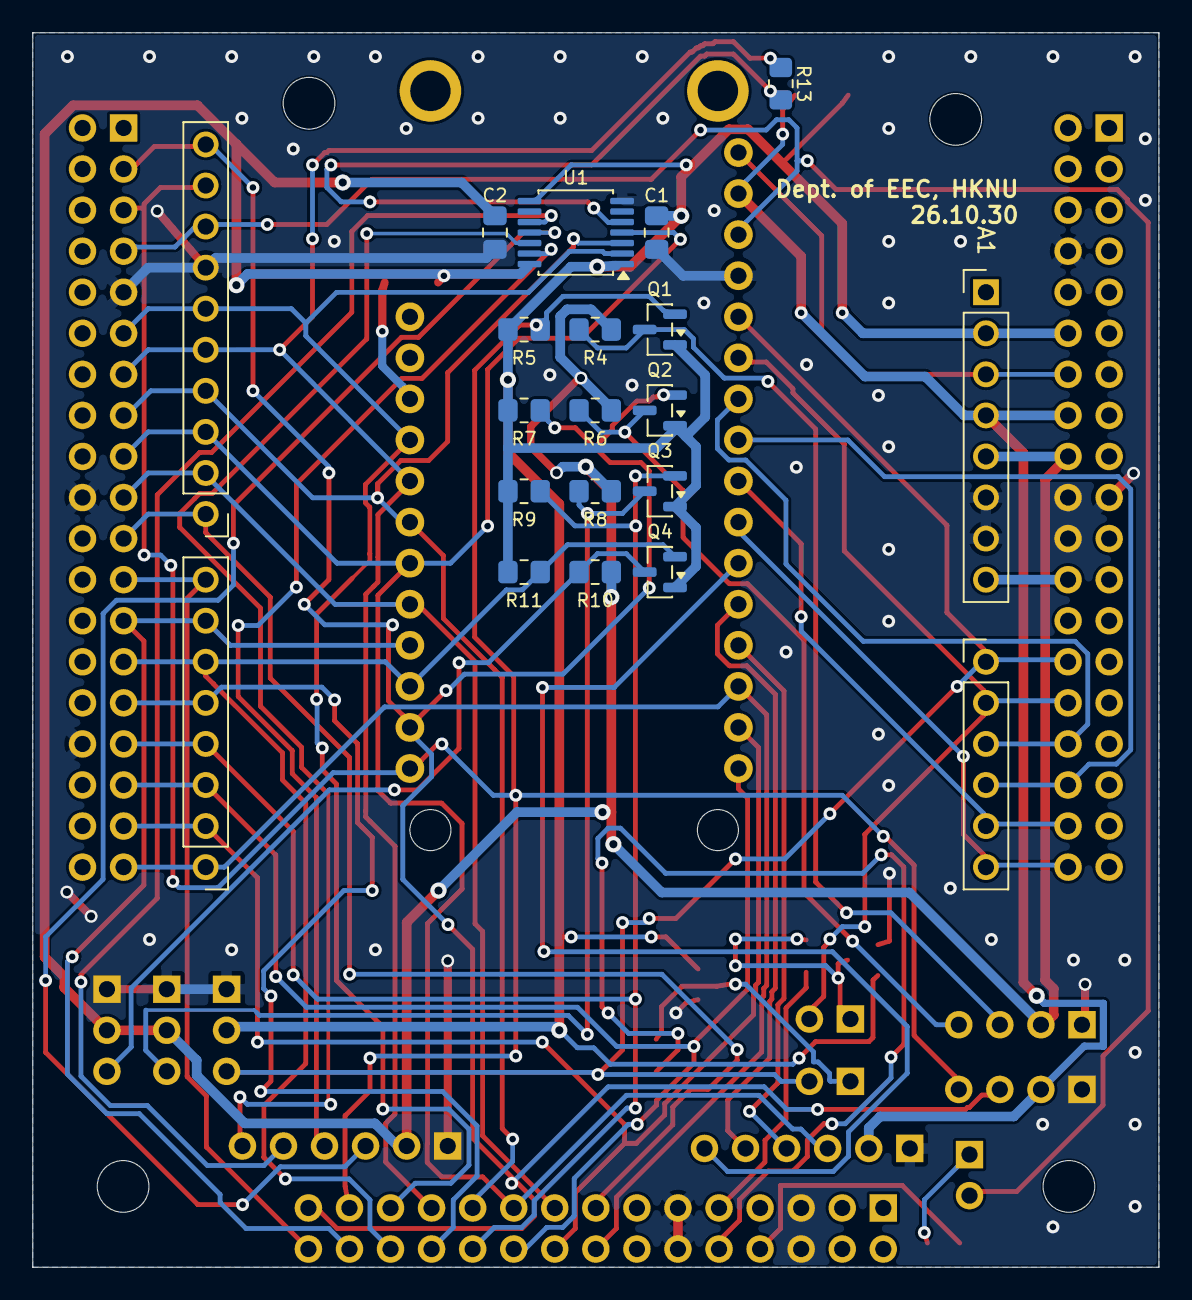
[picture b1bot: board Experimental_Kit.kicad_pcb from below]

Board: 2 copper layers, 69.7 x 76.4 mm, 42 parts (17 on the bottom side), 48 nets.

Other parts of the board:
H1, H2, H3, H4: MountingHole_3.2mm_M3
